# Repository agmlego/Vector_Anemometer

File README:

This project is a modernization of W. Stephen Woodward's vector anemometer, 
detailed in the September 1997 issue of EDN (pp. 114-115, scanned copy found in 
the Doc directory of this repo). This modernization is specifically aimed at 
the small-boat sailing community, but should be able to be easily adapted for 
any wind monitoring project with little effort.

The system will consist of a faithful reproduction of W. Stephen Woodward's 
analog vector anemometer as a masthead wind sensor, with the addition of a 
small microcontroller to read the frequency-based data produced by the circuit. 
The data will be displayed by a series of PWM-dimmable 7-segment displays 
powered by a more powerful microcontroller, placed somewhere in the boat's 
cockpit and connected to the masthead sensor via UART, SPI, or I2C (TBD).

An eventual goal of this project is to allow NMEA 183 passthrough, taking a GPS 
on RS232, displaying select information on the cockpit displays, and injecting 
wind data into the NMEA sentences. An RS232 port will then feed the resulting 
NMEA sentences to a PC host for logging with the aim at automatic creation of 
vehicle polar plots. Alternatively, if budget allows, the system could log such 
data to SD card.

With reference to this repo, the Doc directory contains all relevant 
documentation for the project, including the project BOM, source material, 
notes, and diagrams. Eventually, installation notes and code reference manuals 
will be posted there as well.

The CAD directory will contain any physical CAD drawings, for suggested cases 
and mounting brackets.

The ECAD directory contains all electrical CAD drawings, created using EAGLE 
6.0 or better.

The Code directory contains all relevant code for the system, including a 
formatted version of W. Stephen Woodward's original GW-BASIC code.

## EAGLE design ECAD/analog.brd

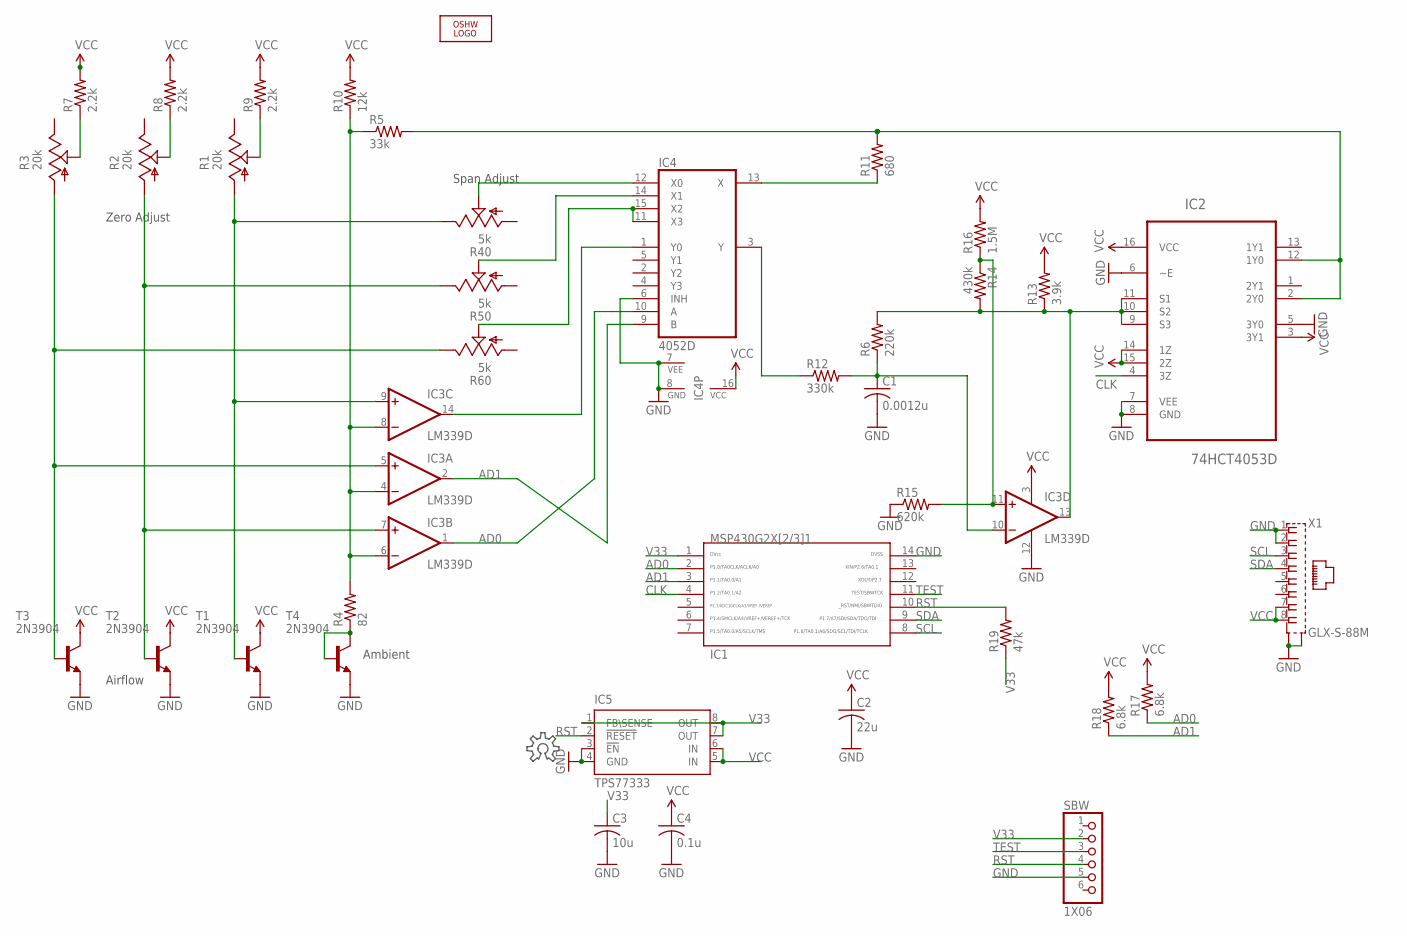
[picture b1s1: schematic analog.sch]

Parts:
C1: 0.0012u; C0805
C2: 22u; C0805
C3: 10u; C0805
C4: 0.1u; C0805
IC1: G2X[2/3]1---PW14; PW14
IC2: 74HCT4053D; SOIC127P600X175-16N
IC3: LM339D; SO14
IC4: 4052D; SO16
IC5: TPS77333
LOGO1: OSHW_LOGO_FILLX0150-NT; OSHW_FILLX150_NOTEXT
R1, R2, R3: 20k; SM-42/43W
R4: 82; M0805
R5: 33k; R0805
R6: 220k; R0805
R7: 2.2k; M0805
R8, R9: 2.2k; R0805
R10: 12k; R0805
R11: 680; R0805
R12: 330k; R0805
R13: 3.9k; R0805
R14: 430k; R0805
R15: 620k; R0805
R16: 1.5M; R0805
R17, R18: 6.8k; M0805
R19: 47k; R0805
R40, R50, R60: 5k; SM-42/43W
SBW: 1X06
T1, T2, T3, T4: 2N3904; TO92
X1: GLX-S-88M

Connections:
AD0: IC1.2, IC3.1 (OUT), IC4.10 (A), R17.1
AD1: IC1.3, IC3.2 (OUT), IC4.9 (B), R18.1
CLK: IC1.4, IC2.4 (3Z)
GND: C1.2, C2.2, C3.2, C4.2, IC1.14, IC2.5 (3Y0), IC2.6 (~E), IC2.7 (VEE), IC2.8 (GND), IC3.12 (GND), IC4.6 (INH), IC4.7 (VEE), IC4.8 (GND), IC5.3 (!EN), IC5.4 (GND), R15.1, SBW.5, T1.3 (E), T2.3 (E), T3.3 (E), T4.3 (E), X1.1, X1.2, X1.S1, X1.S2
unnamed: R4.1, T4.1 (C), T4.2 (B)
unnamed: IC3.9 (+IN), R1.1 (A), R40.3 (E), T1.2 (B)
unnamed: IC4.12 (X0), R40.2 (S)
unnamed: IC4.14 (X1), R50.2 (S)
unnamed: IC4.11 (X3), IC4.15 (X2), R60.2 (S)
unnamed: R3.2 (S), R7.1
unnamed: R2.2 (S), R8.1
unnamed: R1.2 (S), R9.1
unnamed: IC3.4 (-IN), IC3.6 (-IN), IC3.8 (-IN), R4.2, R5.1, R10.1
unnamed: IC3.5 (+IN), R3.1 (A), R60.3 (E), T3.2 (B)
unnamed: IC3.7 (+IN), R2.1 (A), R50.3 (E), T2.2 (B)
unnamed: IC3.14 (OUT), IC4.1 (Y0)
unnamed: IC2.2 (2Y0), IC2.12 (1Y0), R5.2, R11.2
unnamed: IC4.13 (X), R11.1
unnamed: IC4.3 (Y), R12.1
unnamed: C1.1, IC3.10 (-IN), R6.1, R12.2
unnamed: IC2.9 (S3), IC2.10 (S2), IC2.11 (S1), IC3.13 (OUT), R6.2, R13.1, R14.2
unnamed: IC3.11 (+IN), R14.1, R15.2, R16.1
RST: IC1.10, IC5.2 (!RESET), R19.2, SBW.4
SCL: IC1.8, X1.3
SDA: IC1.9, X1.4
TEST: IC1.11, SBW.3
V33: C3.1, IC1.1, IC5.1 (FB\SENSE), IC5.7 (OUT), IC5.8 (OUT), R19.1, SBW.2
VCC: C2.1, C4.1, IC2.3 (3Y1), IC2.14 (1Z), IC2.15 (2Z), IC2.16 (VCC), IC3.3 (V+), IC4.16 (VCC), IC5.5 (IN), IC5.6 (IN), R7.2, R8.2, R9.2, R10.2, R13.2, R16.2, R17.2, R18.2, T1.1 (C), T2.1 (C), T3.1 (C), X1.7, X1.8

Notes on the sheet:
Zero Adjust
Span Adjust
Ambient
Airflow

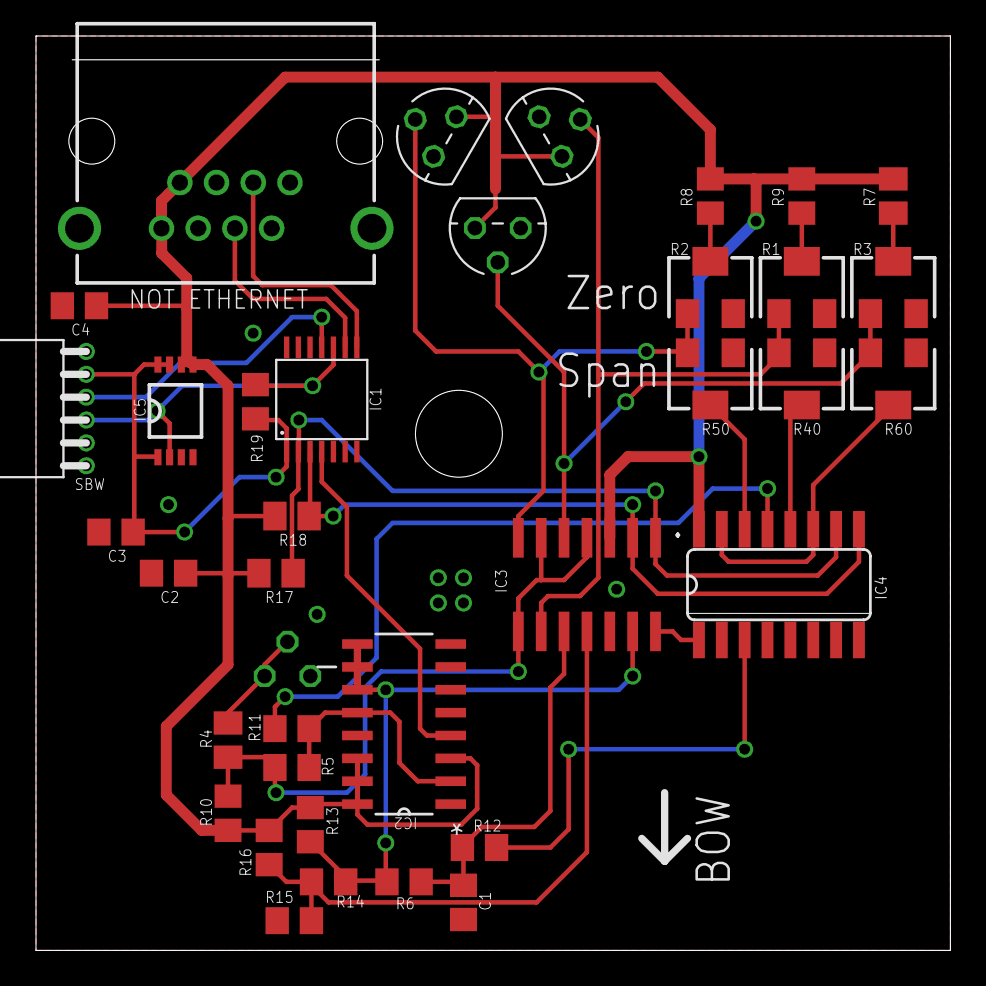
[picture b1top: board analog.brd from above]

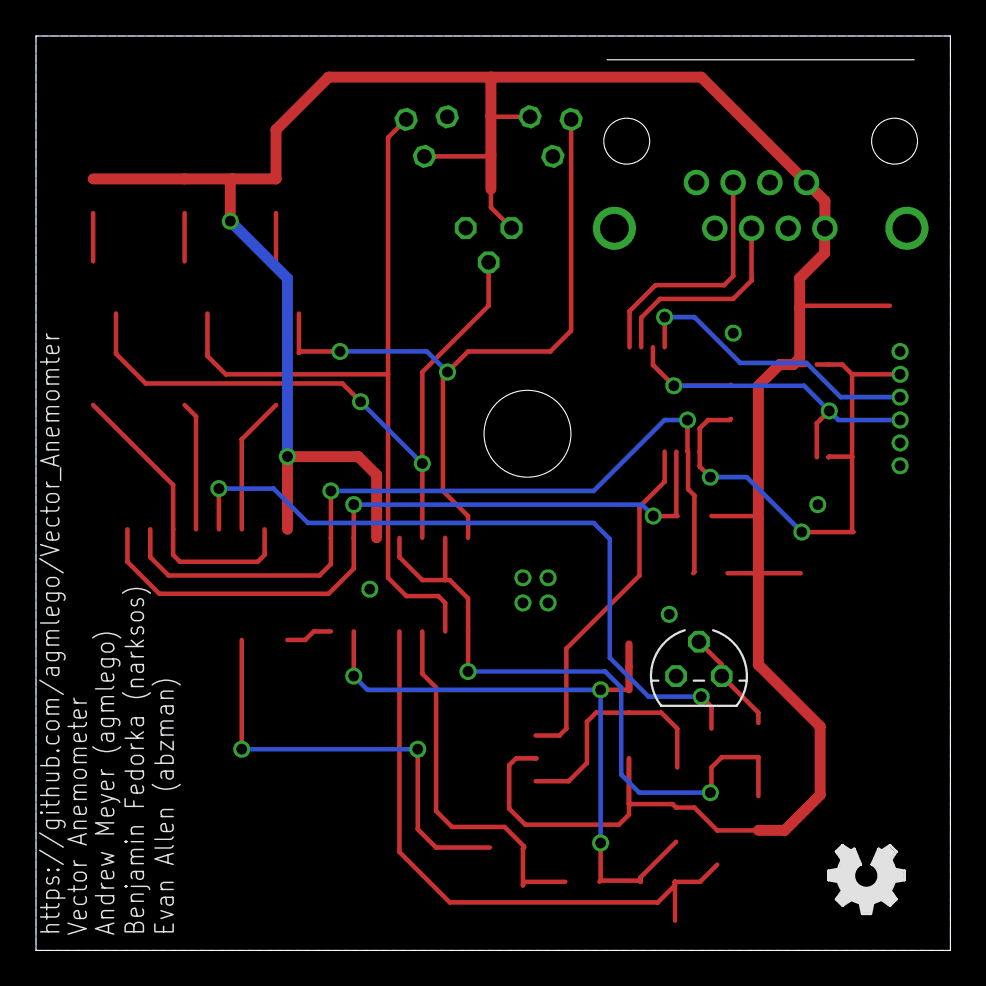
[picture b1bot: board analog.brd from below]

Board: 2 copper layers, 50.8 x 50.8 mm, 38 parts (3 on the bottom side), 28 nets.

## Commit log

2012-07-30 Initial commit of current project files.
2012-07-30 Spellcheck on README, added LICENSE and .gitignore files
2012-07-30 Added documentation on an LED display (LTC-637AX-12) briefly considered for display in this project.
2012-08-25 Began work on PCB artwork, cleaned up schematic a little.
2012-08-25 Formatted README and LICENSE to better flow
2012-08-30 Initial draft layout of analog board. Needs cleanup before routing.
2012-09-17 Added MSP layout to custom.lbr Added MSP micro to schematic (not complete).
2012-09-22 Added MSP430 Spy-By-Wire header, edited layout for production, added and cleaned up silk.
2012-09-26 Added BOM for analog board in ODS format, edited schematic to comply with EAGLE 6.2 rules.
2013-11-25 Replaced SOIC-8 package for TSSOP-8 on TPS77333. Rerouted traces to give more space around the 1/4-20 bolt hole.
2014-08-15 Backup commit before wiping machine

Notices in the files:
parts and their libraries:
SparkFun: Licensing: CC v3.0 Share-Alike You are welcome to use this library for commercial purposes.
